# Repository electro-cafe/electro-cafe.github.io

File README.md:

# Site web de l'Electro Café

[Lien vers le site](https://electro-cafe.github.io/)

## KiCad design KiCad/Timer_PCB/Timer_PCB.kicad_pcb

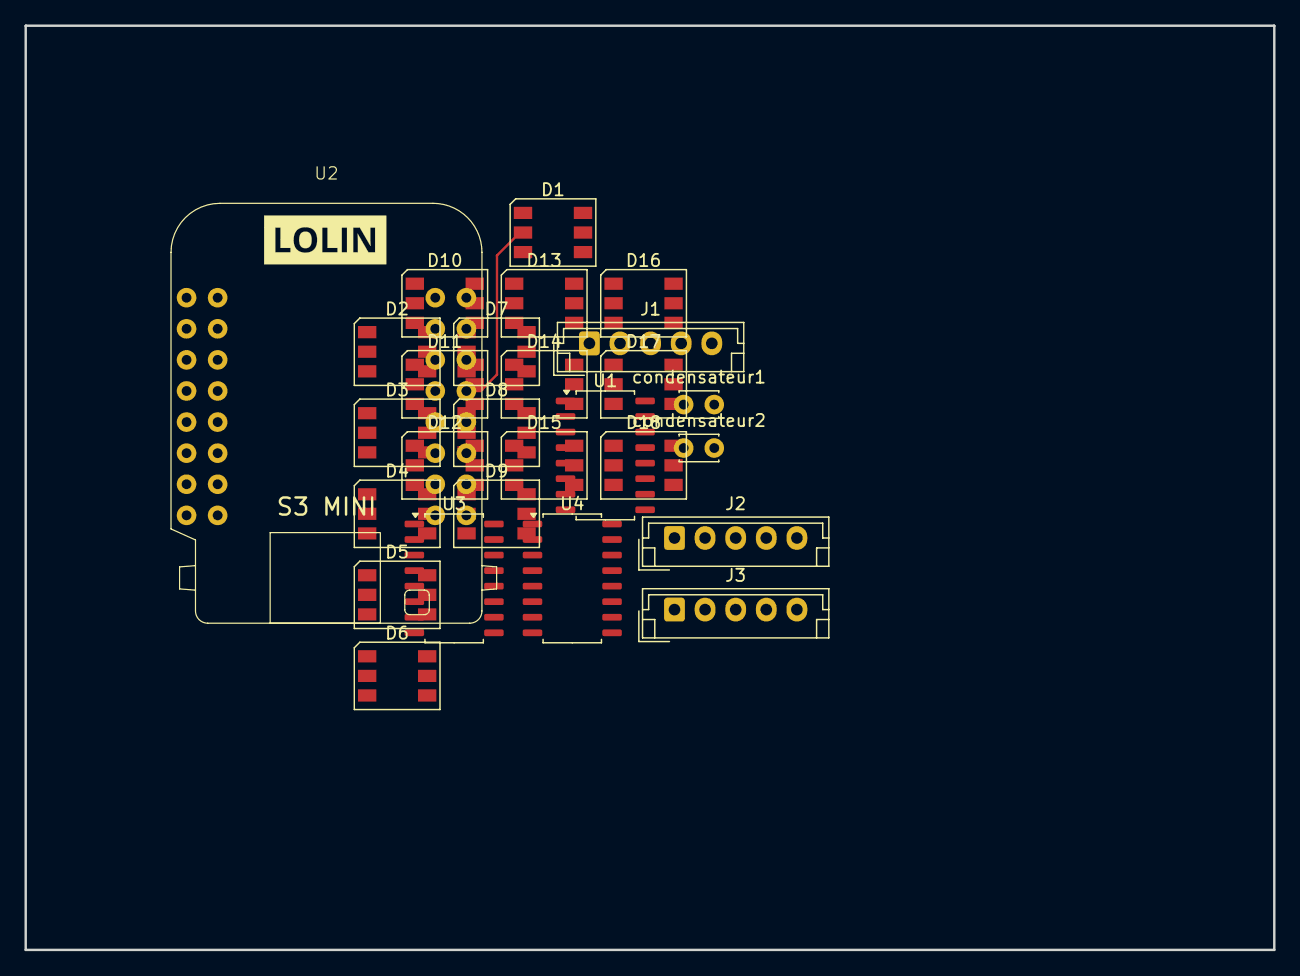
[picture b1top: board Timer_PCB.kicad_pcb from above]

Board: 2 copper layers, 102.0 x 75.5 mm, 27 parts (0 on the bottom side), 44 nets.

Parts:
D1, D2, D3, D4, D5, D6, D7, D8, D9, D10, D11, D12, D13, D14, D15, D16, D17, D18: WS2812; LED_WS2812_PLCC6_5.0x5.0mm_P1.6mm
J1, J2, J3: JST_05; JST_EH_B5B-EH-A_1x05_P2.50mm_Vertical
U1, U3, U4: ULN2003; SOIC-16_4.55x10.3mm_P1.27mm
U2: S3 Mini
condensateur1: 10uF; C_Disc_D3.0mm_W2.0mm_P2.50mm
condensateur2: 100nF; C_Disc_D3.0mm_W2.0mm_P2.50mm

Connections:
+5V: D10.5 (VDD), D11.5 (VDD), D12.5 (VDD), D13.5 (VDD), D14.5 (VDD), D15.5 (VDD), D16.5 (VDD), D17.5 (VDD), D18.5 (VDD), J1.1, J2.1, J3.1, U1.9 (COM), U3.9 (COM), U4.9 (COM)
GND: D1.5 (VDD), D1.6 (VSS), D2.5 (VDD), D2.6 (VSS), D3.5 (VDD), D3.6 (VSS), D4.5 (VDD), D4.6 (VSS), D5.5 (VDD), D5.6 (VSS), D6.5 (VDD), D6.6 (VSS), D7.5 (VDD), D7.6 (VSS), D8.5 (VDD), D8.6 (VSS), D9.5 (VDD), D9.6 (VSS), D10.6 (VSS), D11.6 (VSS), D12.6 (VSS), D13.6 (VSS), D14.6 (VSS), D15.6 (VSS), D16.6 (VSS), D17.6 (VSS), D18.6 (VSS), U1.8 (GND), U3.8 (GND), U4.8 (GND)
M1A: U1.1 (I1), U2.2 (GPIO1)
M1B: U1.2 (I2), U2.5 (GPIO4)
M1C: U1.3 (I3), U2.6 (GPIO5)
M1D: U1.4 (I4), U2.7 (GPIO12)
M2A: U2.8 (GPIO6), U3.1 (I1)
M2B: U2.9 (GPIO13), U3.2 (I2)
M2C: U2.10 (GPIO7), U3.3 (I3)
M2D: U2.11 (GPIO11), U3.4 (I4)
M3A: U2.12 (GPIO8), U4.1 (I1)
M3B: U2.13 (GPIO10), U4.2 (I2)
M3C: U2.14 (GPIO9), U4.3 (I3)
M3D: U2.16 (GPIO14), U4.4 (I4)
unnamed: condensateur1.2, condensateur2.2
unnamed: D1.1 (DOUT), D2.2 (DIN)
unnamed: D2.1 (DOUT), D3.2 (DIN)
unnamed: D3.1 (DOUT), D4.2 (DIN)
unnamed: D4.1 (DOUT), D5.2 (DIN)
unnamed: D5.1 (DOUT), D6.2 (DIN)
unnamed: D6.1 (DOUT), D7.2 (DIN)
unnamed: D7.1 (DOUT), D8.2 (DIN)
unnamed: D8.1 (DOUT), D9.2 (DIN)
unnamed: D10.1 (DOUT), D11.2 (DIN)
unnamed: D11.1 (DOUT), D12.2 (DIN)
unnamed: D12.1 (DOUT), D13.2 (DIN)
unnamed: D13.1 (DOUT), D15.2 (DIN)
unnamed: D14.2 (DIN), D16.1 (DOUT)
unnamed: D14.1 (DOUT), D17.2 (DIN)
unnamed: D15.1 (DOUT), D16.2 (DIN)
unnamed: D17.1 (DOUT), D18.2 (DIN)
unnamed: J1.2, U1.16 (O1)
unnamed: J1.3, U1.15 (O2)
unnamed: J1.4, U1.14 (O3)
unnamed: J1.5, U1.13 (O4)
unnamed: U2.31 (GPIO15), condensateur1.1, condensateur2.1
unnamed: J2.2, U3.16 (O1)
unnamed: J2.3, U3.15 (O2)
unnamed: J2.4, U3.14 (O3)
unnamed: J2.5, U3.13 (O4)
unnamed: J3.2, U4.16 (O1)
unnamed: J3.3, U4.15 (O2)
unnamed: J3.4, U4.14 (O3)
unnamed: J3.5, U4.13 (O4)

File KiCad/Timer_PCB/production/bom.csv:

Designator,Footprint,Quantity,Value,LCSC Part #
CONDENSATEUR1,C_Disc_D3.0mm_W2.0mm_P2.50mm,1,10uF,
CONDENSATEUR2,C_Disc_D3.0mm_W2.0mm_P2.50mm,1,100nF,
"D1, D2, D3, D4, D5, D6, D7, D8, D9",LED_WS2812_PLCC6_5.0x5.0mm_P1.6mm,9,WS2812,
J1,JST_EH_B5B-EH-A_1x05_P2.50mm_Vertical,1,JST_05,
U1,SOIC-16_4.55x10.3mm_P1.27mm,1,ULN2003,C7512
U2,S3 Mini,1,~,

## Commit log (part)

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2025-02-15 Add README file with project description and link
2025-02-15 Remove caching step for virtual environment in GitHub Actions workflow
2025-02-16 Create article_1_liste_materiel.md
    ajout d'un article au blog
2025-02-16 Create blog_article_1_logiciel_materiel
    ajout d'un article de blog listant le matériel et les logiciels
2025-02-16 Delete article_1_liste_materiel.md
    delete file
2025-02-16 Rename blog_article_1_logiciel_materiel to article_1_logiciel_materiel
    changé nom de l'article
2025-02-16 Rename article_1_logiciel_materiel to article_1_logiciel_materiel.md
2025-02-16 Update mkdocs.yml
    ajout d'un article au blog
2025-02-22 ajout du membre thomas Fessler
2025-02-22 Update article_1_logiciel_materiel.md
    ajout du matériel commandé
2025-02-22 correction article blog et ajout autheur thomas
2025-02-22 ajout d'un draft
2025-02-22 ajout site dans fichier gitignore
2025-02-22 Remove draft article and clean up blog post metadata
2025-02-22 ajout d'un article sur mkdocs markdown expliquant comment prévisualiser les changements en local et comment publier les changements sur github
2025-02-22 description mkdocs, markdown et processus pour consulter le blog en local ainsi que le push sur git
2025-02-22 essai changement path images
2025-02-22 try to fix image path
2025-02-22 Update image paths in Mkdocs documentation and add new images; enable md_in_html extension
2025-02-22 correction orthographe description autheur thomas. ajout section sur le chemin d'accès des images et leur intégration dans mkdocs. Ajout section sur gitbash expliquant comment synchroniser sa version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
2025-03-02 ajout de la catégorie formule, début de l'article sur les définitions et formules liées à l'électronique
2025-03-02 ajout tableau définition voc électronique
2025-03-02 avanc de l'article fondamentales de l'électronique. Work in progress
2025-03-04 ajout d'unité et de leurs relations dans l'article fondamentales de l'électronique. WIP
2025-03-05 ajout extension KaTeX dans le css et arithmatex dans mkdocs.yml pour inscrire correctement les formules. finalisation de l'article sur les formules, les nominations et les unités.
2025-03-07 finalisation article fondamentales électronique. ajout loi kirshhoff et sources
2025-03-07 correction mise en page
2025-03-09 MAJ formules+expliation loi des mailles creation article materiel electronique creation article Arduino IDE set up
2025-03-16 création article détaillant les led WS2812 et le signal PWM. Ajout tableau dans la section fondamentales electricité détaillant la différence tension et intensité dans montage en série / parallèle
2025-03-16 ajout image section signal digital analogique
2025-03-20 ajout dossier contenant code Arduino de test Esp 3 led + switch
    y
2025-03-30 ajout d'un fichier illustrator contenant des schéma électriques et image d'interupteur 3 points
2025-04-04 updated arduino rainbow code for 3point switch button use
2025-04-05 ajout de schéma de cablage pour déterminer la position d'un bouton 3 points avec 2 pin. explication des termes pull up et pull down. explication d'un diviseur de tension dans l'article led WS2812 et 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
2025-04-13 ajout de théorie sur la représentation des nombres à virgules, corrections diverses schéma electrique resistance interne pull up. ajout d'une courte définition des 4 types de languagess. ajout de déf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
2025-04-17 ajout code Arduino intégrant la fonction rainbow et l'usage du bouton 3 position
2025-04-21 ajout d'une section sur le terminal, ses commandes et controle et nouvel appelation pour l'article traitant de mkdocs et github..
    ajout d'une section sur comment créer un nouvel article mkdocs dans l'article traitant de mkdocs et github
    ajout d'un article sur les formules mathématiques et identités ramarquables + factorisation. ne traite que des puissance négatives et des doubles divisions pour l'instant.
2025-04-25 add stepper control in arduino code controlling led
2025-04-27 ajout d'une section sur les factoriel dans l'article traitant des math. ajout de plusieurs composant (capacitor, step motor 28byj-48, neopixel ws2812) dans l'article traitant des composants electroni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
2025-05-01 dans l'article c++, ajout de définition et de comparatif afin de mieux expliquer et comprendre les liens et différence entre les classes, objets, constructeurs, méthodes, déclaration, définition etc
2025-05-02 ajout d'exemple et développement de l'article C++. différence entre const et static. présentation des constructeur défini hors variable, de l'héritage de classe, de la création d'objets et de la créa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
2025-05-04 ajout du model 3D blender dans le dossier ressources. ajout du composant batterie lipo dans l'article composants electronique et outil. ajout de symbole au tableau des composants electronique de l'ar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
2025-05-04 début de repartition du code dans plusieurs fichier header et cpp
2025-05-06 ajout de la définition du datatype long et unsigned dans l'article c++ ajout d'un tutoriel sur comment utiliser l'oscilloscope pour lire le signal du stepper dans la section composant electronique et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
    ajout de blocking échelle 1 carré = 1cm dans le fichier blender.
    composant block: stepper et control board stepper.
2025-05-08 fractionnement du code en sous dossier débuté. j'ai cleané le code du stepper pour avoir que le cas à 4 pin et l'ai commenté
2025-05-09 création de 3 objets stepmotor pour les minutes/heures/jours dans le main du code timer
2025-05-13 l'article sur l'oscilloscope n'a pas été synchronisé. je met à jour
2025-05-13 ajout article oscilloscope
2025-05-13 ajout et détail des strapping pins dans la section élément de l'esp 32 de l'article communication ESP32-composants
2025-05-19 étoffage section step motor. ajout schéma bipolaire et unipolaire ainsi qu'explication. ajout explication regle main droite determination direction du pole Nord. Ajout de l'article Kicad qui explique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
2025-05-22 mise à jour du fichier kicad
2025-05-24 Ajout de la différenciation SMD et THT dans l'article composants electroniques. Ajout de la marche à suivre pour passer d'un composant physique à la réalisation de son schematic sur kicad. recherche 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
2025-05-25 avancement kicad
2025-05-29 avancement de l'article sur l'utilisation de Kicad
2025-06-04 dévellopement de l'article Kicad. Comment parametrer nbr couches PCB et créer zone connecté GND
2025-06-09 completion de l'article Kicad (BOM / renommer les éléments de la schématique). Mise à jour des fichier kicad. circuit imprimé plus propre.
2025-07-11 ajout d'une section ESP_IDF, explication sur comment installer cet environement de dévelopement sur VSCode, troubleshoot et fonctions principales pour compiler et executer le code
2025-07-12 Ajout d'un article sur JLCPCB, décrivant comment passer commande d'un PCB,. Différence entre code conventionel de footprint et dimension du footprint. Dans l'article Kicad, ajout marche à suivre sur 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
2025-07-20 MAJ article ESP_IDF, pas encore terminé. Création d'un article sur les réseaux
2025-07-22 ajout détail sur PCBA economic et standard dans l'article JLCPCB
2025-08-07 Mise à jour Modele 3D
2025-08-17 détail et schéma protocole de communication i2c uart et spi
2025-08-27 mise à jour fichier 3D - travail en cours
2025-09-03 finalisation V1 fichier blender casing. Reste à préparer chaque pièce dans la bonne orientation et les exporter puis ajuster zone fill 100% dans prusa slicer
2025-09-11 mise à jour article esp idf sur la partie upload vers esp idf via github. work in progress
2025-09-12 mise à jour article ESP IDF: upload component vers esp Registry via github. Work in progress clarification remerciement fichiers Jacques
2025-09-12 mise à jour de l'article esp idf décrivant comment uploader un component sur esp registry
2025-09-15 cookieCutter utilisation
2025-09-17 comment crée un repo git à partir d'un dossier local
2025-09-24 MAJ fichier 3D et article imprimante 3D
2025-09-28 MAJ article c++
2025-09-28 détail sur classes dérivées
2025-10-06 ajout article lookup table bit masking et operation logiques
2025-10-19 mise a jour article esp_idf_avec FreeRTOS
2025-10-21 mise a jour fichier blender
2025-10-25 Mise a jour modele 3D
2025-10-25 complement article FreeRTOS queue
2025-11-08 ajout information debug ESP-IDF mode download
2025-11-09 ajout commande de build verbeux sur article esp_idf
2025-11-09 correction comande comit verbeux
2025-11-16 précision accès attributs classe parent au sein de classe derivée via virtual et override
2025-11-18 ajout section debug dans article esp_idf ajout detail acces member dans les classes derivee article C++
2025-11-21 mise a jour article esp idf avec info debug.
2025-11-23 MAJ article opérateur binaire. ajout section operateur logique
2025-11-30 complement article debug et ajout schema bitmasking
2025-12-02 MAJ article inclusion de component de ESP Registry
2025-12-11 ajout base freertosTimer dans l'article ESP_IDF
2025-12-18 ajout section décomposiition d'un hexacode en composant rvb via bitmasking et bitshifting
2026-01-08 Ajout infos pull request. ajout section pointeur vs reference dans article C++
2026-01-08 ajout section reference vs pointeur dans article C++
2026-01-23 ajout section vector et correction section struct
2026-01-25 article gamma et comment integret diagrames mermaid dans mkdocs
2026-01-27 ajout section mermaid uml dans article C++
2026-01-28 MAJ case study UML diagram
2026-02-28 ButtonPanel moved to the right directory no diming on stop and color change mode motor enter sleep when inactive for 30ms
2026-03-01 ajout exemple cmakelists
2026-03-17 ajout article programme et executable
2026-05-14 ajout contenu sur l'electricite et les variables la composant. Ajout info PlatformIO ajout début info ESP NOW
2026-05-14 ajout section suppression d'un repo git mise a jour guide crer repository sur git a partir d'un dossier local
2026-06-03 ajout section AR
2026-06-03 ajout section AR image target
2026-06-17 ajout paragraphe utilisation de platformIO et composant simplefoc mini. developpement marche à suivre 8th wall
2026-06-25 ajout doc teleplot
